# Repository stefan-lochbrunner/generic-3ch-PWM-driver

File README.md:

Generic 3-channel PWM driver for analog RGB LEDs. To be used with separate MCU that connects via header.

2nd version based on ATtiny x5 that can be controlled by an ESP8266, possibly also via IR or buttons.

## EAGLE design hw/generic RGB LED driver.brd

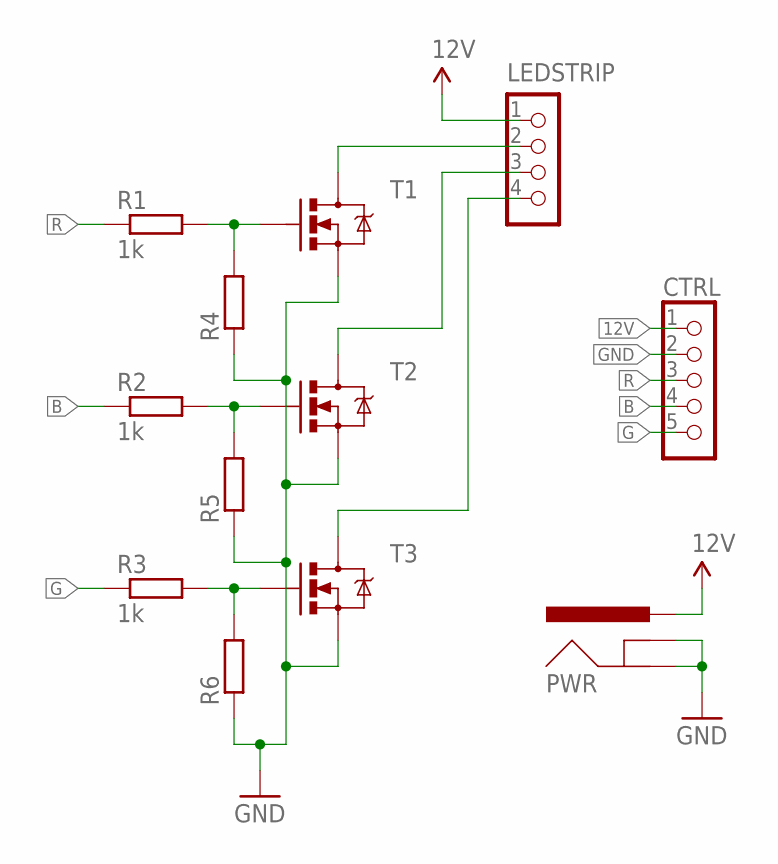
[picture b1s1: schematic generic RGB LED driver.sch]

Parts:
CTRL: CON_HEADER_1X05-PTH; M1X5
LEDSTRIP: 12vBRG; M1X4
PWR: POWER_JACKPTH; POWER_JACK_PTH
R1, R2, R3: 1k; R603
R4, R5, R6: RESISTOR-0603; R603
T1, T2, T3: MOSFET-NCHANNELFDD8780; DPAK

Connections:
12V: CTRL.1, LEDSTRIP.1, PWR.PWR
B: CTRL.4, R2.1
G: CTRL.5, R3.1
GND: CTRL.2, PWR.GND, PWR.GNDBREAK, R4.1, R5.1, R6.1, T1.3 (S), T2.3 (S), T3.3 (S)
unnamed: R1.2, R4.2, T1.1 (G)
unnamed: R2.2, R5.2, T2.1 (G)
unnamed: R3.2, R6.2, T3.1 (G)
unnamed: LEDSTRIP.2, T1.4 (D)
unnamed: LEDSTRIP.3, T2.4 (D)
unnamed: LEDSTRIP.4, T3.4 (D)
R: CTRL.3, R1.1

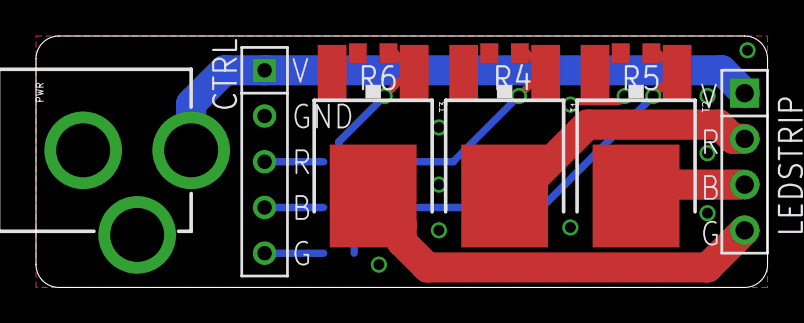
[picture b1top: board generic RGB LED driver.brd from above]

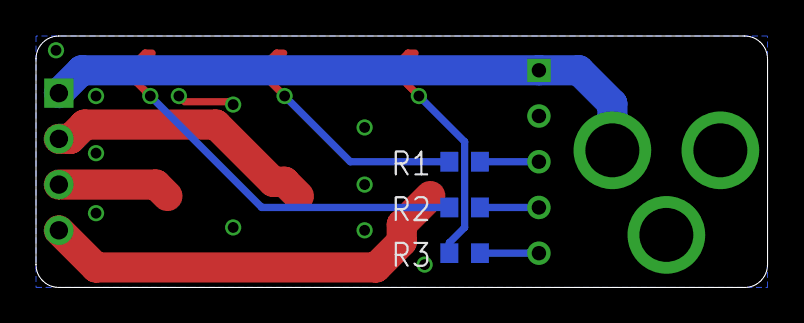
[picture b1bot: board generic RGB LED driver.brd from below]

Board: 2 copper layers, 40.6 x 14.0 mm, 12 parts (3 on the bottom side), 11 nets.

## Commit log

2015-07-09 :tada: Added .gitattributes
2015-07-16 restructured hw, added even more generic driver

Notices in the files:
parts and their libraries:
SparkFun-Connectors: Licensing: Creative Commons ShareAlike 4.0 International - https://creativecommons.org/licenses/by-sa/4.0
